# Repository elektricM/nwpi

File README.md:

# NWPi - NumWorks Pi Power Module

Power module PCB for running a Raspberry Pi Zero inside a NumWorks calculator.

## Specs
- **Input:** USB 5V 1A
- **Battery:** 3.7V LiPo (TP4056 charger, 600mA)
- **Output:** 5V 1.5A (SX1308 boost)
- **Size:** 19 × 20.5mm

## Components
- TP4056 - LiPo charger IC
- SX1308 - Boost converter
- SS34 - Schottky diode
- 4.7µH inductor

## Files
- `nwpi.kicad_sch` - Schematic
- `nwpi.kicad_pcb` - PCB layout
- `production/` - Gerbers for JLCPCB

## License
MIT

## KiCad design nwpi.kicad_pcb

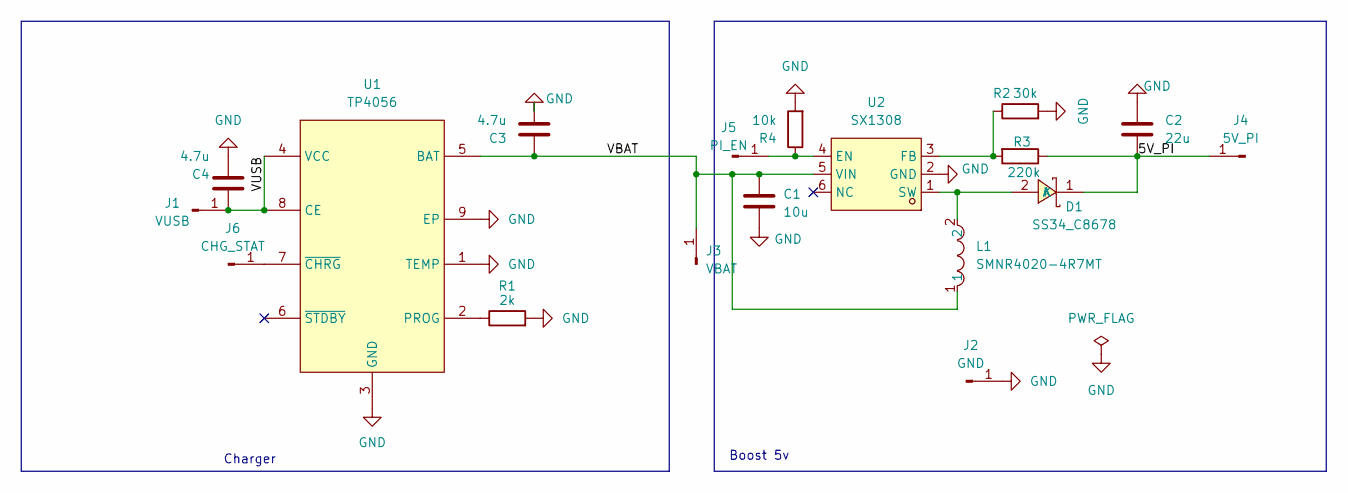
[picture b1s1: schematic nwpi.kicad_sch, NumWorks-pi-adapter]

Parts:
C1: 10u; C_0603_1608Metric
C2: 22u; C_0805_2012Metric
C3, C4: 4.7u; C_0603_1608Metric
D1: SS34_C8678; SMA_L4.3-W2.6-LS5.2-RD; LCSC Part C8678
J1: VUSB; WiredPad_3x2mm
J2: GND; WiredPad_3x2mm
J3: VBAT; WiredPad_3x2mm
J4: 5V_PI; WiredPad_3x2mm
J5: PI_EN; WiredPad_3x2mm
J6: CHG_STAT; WiredPad_3x2mm
L1: SMNR4020-4R7MT; IND-SMD_L4.0-W4.0_SMNR4020; LCSC Part C467061
R1: 2k; R_0402_1005Metric
R2: 30k; R_0603_1608Metric
R3: 220k; R_0603_1608Metric
R4: 10k; R_0402_1005Metric
U1: TP4056; ESOP-8_L4.9-W3.9-P1.27-LS6.0-BL-EP; LCSC Part C16581
U2: SX1308; SOT-23-6_L2.9-W1.6-P0.95-LS2.8-BL; LCSC Part C78162

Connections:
/5V_PI: C2.1, D1.1 (K), J4.1, R3.1
/VBAT: C1.1, C3.1, J3.1, L1.1, U1.5 (BAT), U2.5 (VIN)
/VUSB: C4.1, J1.1, U1.4 (VCC), U1.8 (CE)
GND: C1.2, C2.2, C3.2, C4.2, J2.1, R1.2, R2.2, R4.2, U1.1 (TEMP), U1.3 (GND), U1.9 (EP), U2.2 (GND)
unnamed: D1.2 (A), L1.2, U2.1 (SW)
unnamed: J5.1, R4.1, U2.4 (EN)
unnamed: J6.1, U1.7 (~CHRG)
unnamed: R1.1, U1.2 (PROG)
unnamed: R2.1, R3.2, U2.3 (FB)

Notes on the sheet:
Charger
Boost 5v

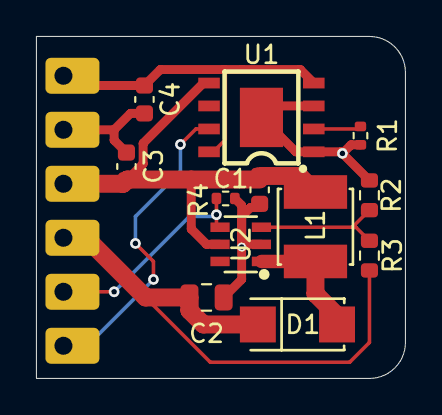
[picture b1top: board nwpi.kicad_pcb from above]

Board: 2 copper layers, 20.5 x 19.0 mm, 18 parts (0 on the bottom side), 9 nets.

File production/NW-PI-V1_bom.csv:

Designator,Footprint,Quantity,Value,LCSC Part #
C1,0603,1,10u,
C2,0805,1,22u,
"C3, C4",0603,2,4.7u,
D1,SMA_L4.3-W2.6-LS5.2-RD,1,SS34_C8678,
J1,WiredPad_3x2mm,1,VUSB,
J2,WiredPad_3x2mm,1,GND,
J3,WiredPad_3x2mm,1,VBAT,
J4,WiredPad_3x2mm,1,5V_PI,
J5,WiredPad_3x2mm,1,PI_EN,
J6,WiredPad_3x2mm,1,CHG_STAT,
L1,IND-SMD_L4.0-W4.0_SMNR4020,1,SMNR4020-4R7MT,C467061
R1,0402,1,2k,
R2,0603,1,30k,
R3,0603,1,220k,
R4,0402,1,10k,
U1,ESOP-8_L4.9-W3.9-P1.27-LS6.0-BL-EP,1,TP4056,
U2,SOT-23-6_L2.9-W1.6-P0.95-LS2.8-BL,1,SX1308,

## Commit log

2026-02-08 Initial commit: NWPi v1.0 power module for NumWorks Pi
